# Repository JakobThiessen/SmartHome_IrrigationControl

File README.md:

# SmartHome_IrrigationControl

test

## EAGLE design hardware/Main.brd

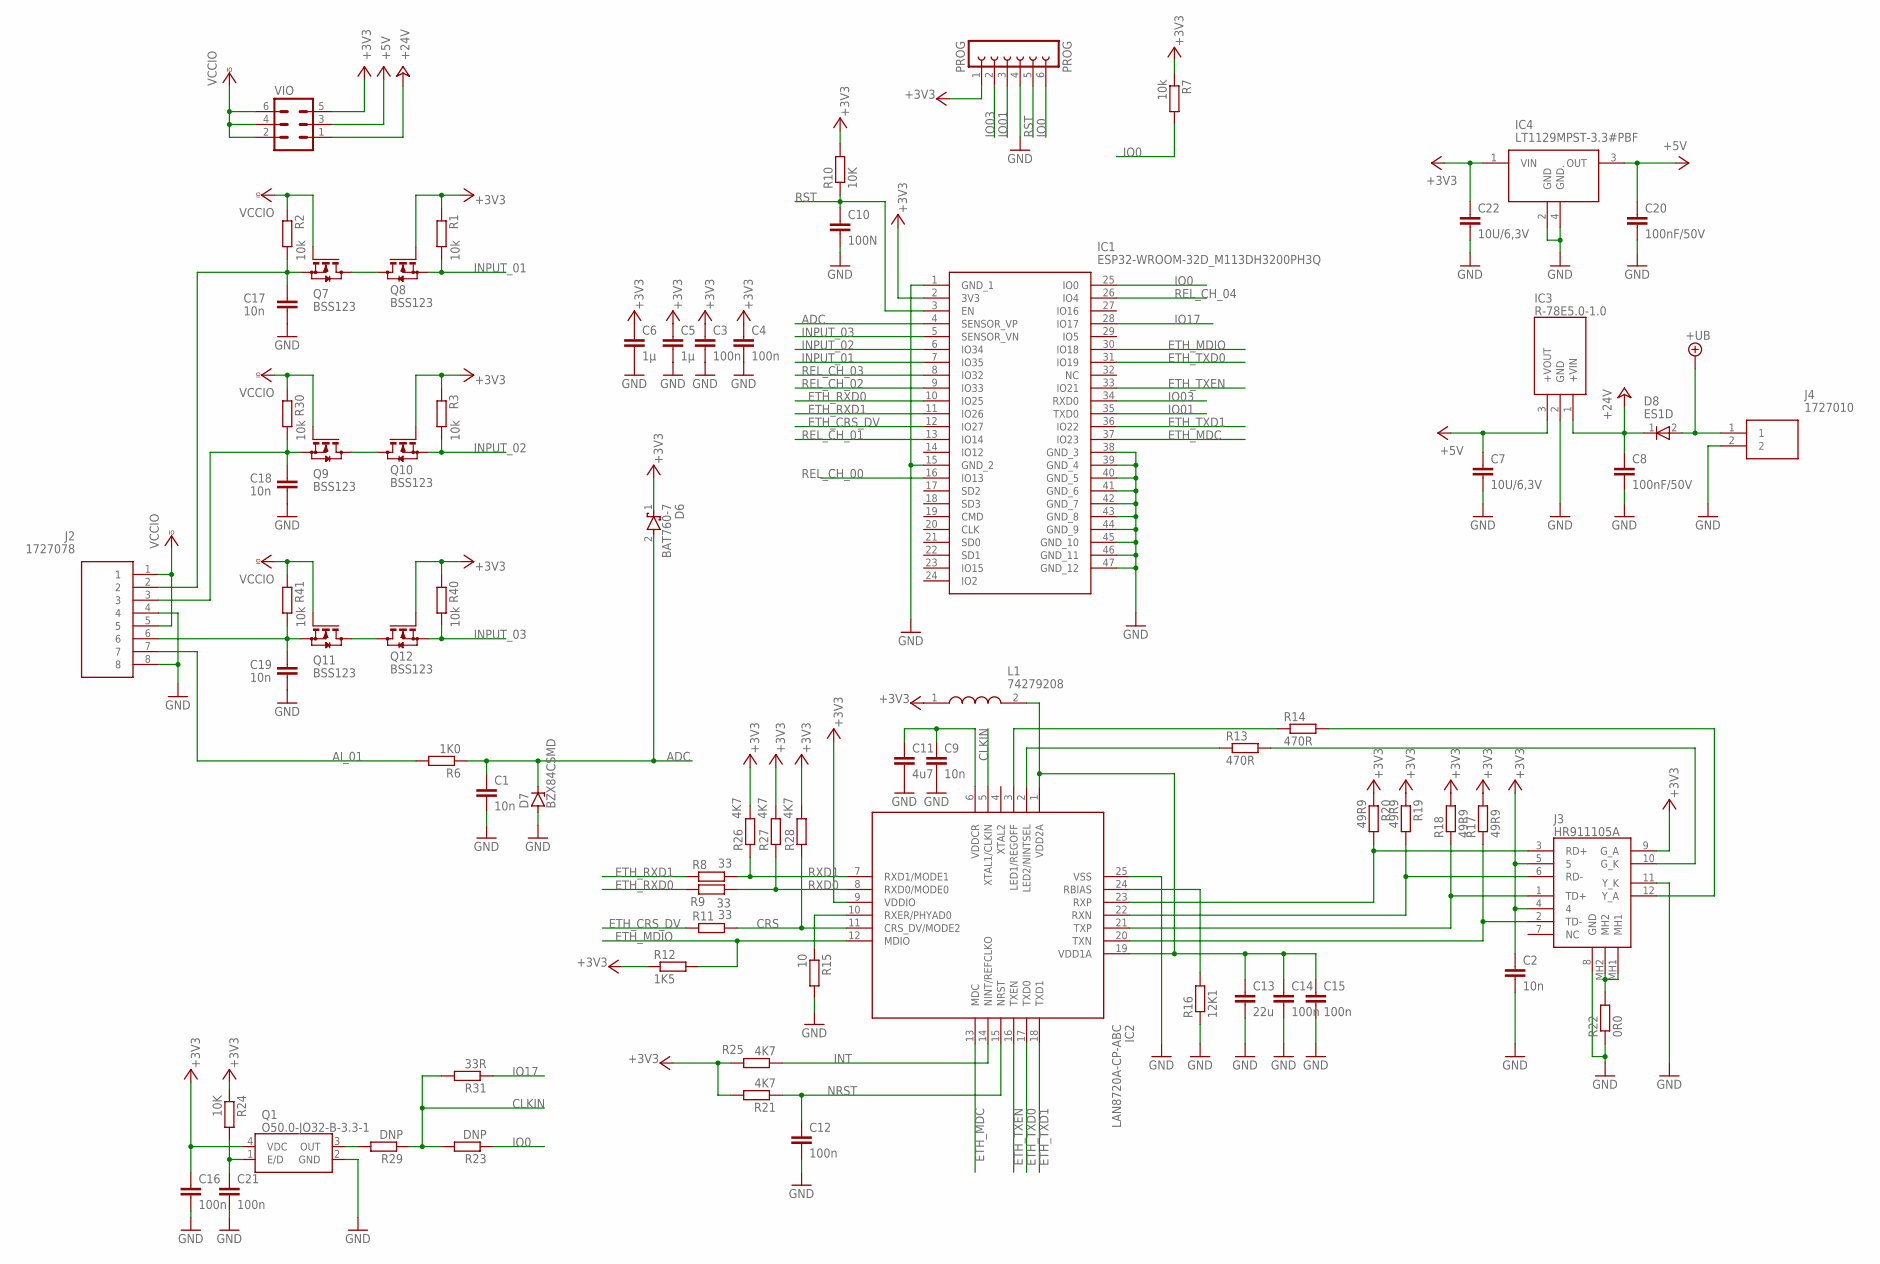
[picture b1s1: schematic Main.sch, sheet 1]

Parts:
C1, C2, C9, C17, C18, C19: 10n; C0603
C3, C4, C12, C14, C15, C16, C21: 100n; C0603
C5, C6: 1µ; C0603
C7, C22: 10U/6,3V; C0603
C8, C20: 100nF/50V; C0603
C10: 100N; C0603
C11: 4u7; C0603
C13: 22u; C0603
D6: BAT760-7; SOD2513X120N
D7: BZX84CSMD; TO236
D8: ES1D; SODFL3618X143N
IC1: ESP32-WROOM-32D_M113DH3200PH3Q; ESP32WROOM32DM113DH3200PH3Q0
IC2: LAN8720A-CP-ABC; QFN50P400X400X100-25N
IC3: R-78E5.0-1.0; R78E3310
IC4: LT1129MPST-3.3#PBF; SOT230P700X180-4N
J2: 1727078
J3: HR911105A
J4: 1727010
L1: 74279208; CAPC2012X90N
PROG: PROG; FE06
Q1: O50.0-JO32-B-3.3-1; O200JO32B1V31T1LF
Q7, Q8, Q9, Q10, Q11, Q12: BSS123; SOT23
R1, R2, R3, R7, R30, R40, R41: 10k; R0603
R6: 1K0; R0603
R8, R9, R11: 33; R0603
R10, R24: 10K; R0603
R12: 1K5; R0603
R13, R14: 470R; R0603
R15: 10; R0603
R16: 12K1; R0603
R17, R18, R19, R20: 49R9; R0603
R21, R25, R26, R27, R28: 4K7; R0603
R22: 0R0; R0603
R23, R29: DNP; R0603
R31: 33R; R0603
VIO: MA03-2

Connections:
+3V3: C2.1, C3.1, C4.1, C5.1, C6.1, C16.1, C22.1, D6.1 (K), IC1.2 (3V3), IC2.9 (VDDIO), IC4.1 (VIN), J3.4, J3.5, J3.9 (G_A), L1.1, PROG.1, Q1.4 (VDC), Q8.1 (G), Q10.1 (G), Q12.1 (G), R1.1, R3.1, R7.1, R10.2, R12.1, R17.2, R18.2, R19.1, R20.1, R21.2, R24.1, R25.2, R26.2, R27.2, R28.2, R40.1, VIO.5
+5V: C7.1, C20.1, IC3.3 (+VOUT), IC4.3 (OUT), VIO.3; also elsewhere on the board
+24V: C8.1, D8.1 (K), IC3.1 (+VIN), VIO.1
+UB: D8.2 (A), J4.1; also elsewhere on the board
ADC: C1.1, D6.2 (A), D7.C, IC1.4 (SENSOR_VP), R6.1
AI_01: J2.7, R6.2
CLKIN: IC2.5 (XTAL1/CLKIN), R23.2, R29.1, R31.2
CRS: IC2.11 (CRS_DV/MODE2), R11.2, R28.1
ETH_CRS_DV: IC1.12 (IO27), R11.1
ETH_MDC: IC1.37 (IO23), IC2.13 (MDC)
ETH_MDIO: IC1.30 (IO18), IC2.12 (MDIO), R12.2
ETH_PHY_PWR: C21.1, Q1.1 (E/D), R24.2
ETH_RXD0: IC1.10 (IO25), R9.1
ETH_RXD1: IC1.11 (IO26), R8.1
ETH_TXD0: IC1.31 (IO19), IC2.17 (TXD0)
ETH_TXD1: IC1.36 (IO22), IC2.18 (TXD1)
ETH_TXEN: IC1.33 (IO21), IC2.16 (TXEN)
GND: C1.2, C2.2, C3.2, C4.2, C5.2, C6.2, C7.2, C8.2, C9.2, C10.2, C11.2, C12.2, C13.2, C14.2, C15.2, C16.2, C17.2, C18.2, C19.2, C20.2, C21.2, C22.2, D7.A, IC1.1 (GND_1), IC1.15 (GND_2), IC1.38 (GND_3), IC1.39 (GND_4), IC1.40 (GND_5), IC1.41 (GND_6), IC1.42 (GND_7), IC1.43 (GND_8), IC1.44 (GND_9), IC1.45 (GND_10), IC1.46 (GND_11), IC1.47 (GND_12), IC2.25 (VSS), IC3.2 (GND), IC4.2 (GND), IC4.4 (GND.), J2.4, J2.8, J3.8 (GND), J3.11 (Y_K), J4.2, PROG.4, Q1.2 (GND), R15.2, R16.1, R22.1; also elsewhere on the board
INPUT_01: IC1.7 (IO35), Q8.2 (S), R1.2
INPUT_02: IC1.6 (IO34), Q10.2 (S), R3.2
INPUT_03: IC1.5 (SENSOR_VN), Q12.2 (S), R40.2
INT: IC2.14 (NINT/REFCLKO), R25.1
IO0: IC1.25 (IO0), PROG.6, R7.2, R23.1
IO01: IC1.35 (TXD0), PROG.3
IO03: IC1.34 (RXD0), PROG.2
IO17: IC1.28 (IO17), R31.1
unnamed: IC2.20 (TXN), J3.2 (TD-), R17.1
unnamed: IC2.22 (RXN), J3.6 (RD-), R19.2
unnamed: IC2.23 (RXP), J3.3 (RD+), R20.2
unnamed: J3.12 (Y_A), R14.2
unnamed: J3.10 (G_K), R13.2
unnamed: Q1.3 (OUT), R29.2
unnamed: J3.MH1, J3.MH2, R22.2
unnamed: Q7.3 (D), Q8.3 (D)
unnamed: Q9.3 (D), Q10.3 (D)
unnamed: C17.1, J2.2, Q7.2 (S), R2.2
unnamed: C13.1, C14.1, C15.1, IC2.1 (VDD2A), IC2.19 (VDD1A), L1.2
unnamed: C9.1, C11.1, IC2.6 (VDDCR)
unnamed: IC2.2 (LED2/NINTSEL), R13.1
unnamed: IC2.3 (LED1/REGOFF), R14.1
unnamed: IC2.10 (RXER/PHYAD0), R15.1
unnamed: IC2.21 (TXP), J3.1 (TD+), R18.1
unnamed: IC2.24 (RBIAS), R16.2
unnamed: C18.1, J2.3, Q9.2 (S), R30.2
unnamed: Q11.3 (D), Q12.3 (D)
unnamed: C19.1, J2.6, Q11.2 (S), R41.2
NRST: C12.1, IC2.15 (NRST), R21.1
REL_CH_00: IC1.16 (IO13); also elsewhere on the board
REL_CH_01: IC1.13 (IO14); also elsewhere on the board
REL_CH_02: IC1.9 (IO33); also elsewhere on the board
REL_CH_03: IC1.8 (IO32); also elsewhere on the board
REL_CH_04: IC1.26 (IO4); also elsewhere on the board
RST: C10.1, IC1.3 (EN), PROG.5, R10.1
RXD0: IC2.8 (RXD0/MODE0), R9.2, R27.1
RXD1: IC2.7 (RXD1/MODE1), R8.2, R26.1
VCCIO: J2.1, J2.5, Q7.1 (G), Q9.1 (G), Q11.1 (G), R2.1, R30.1, R41.1, VIO.2, VIO.4, VIO.6

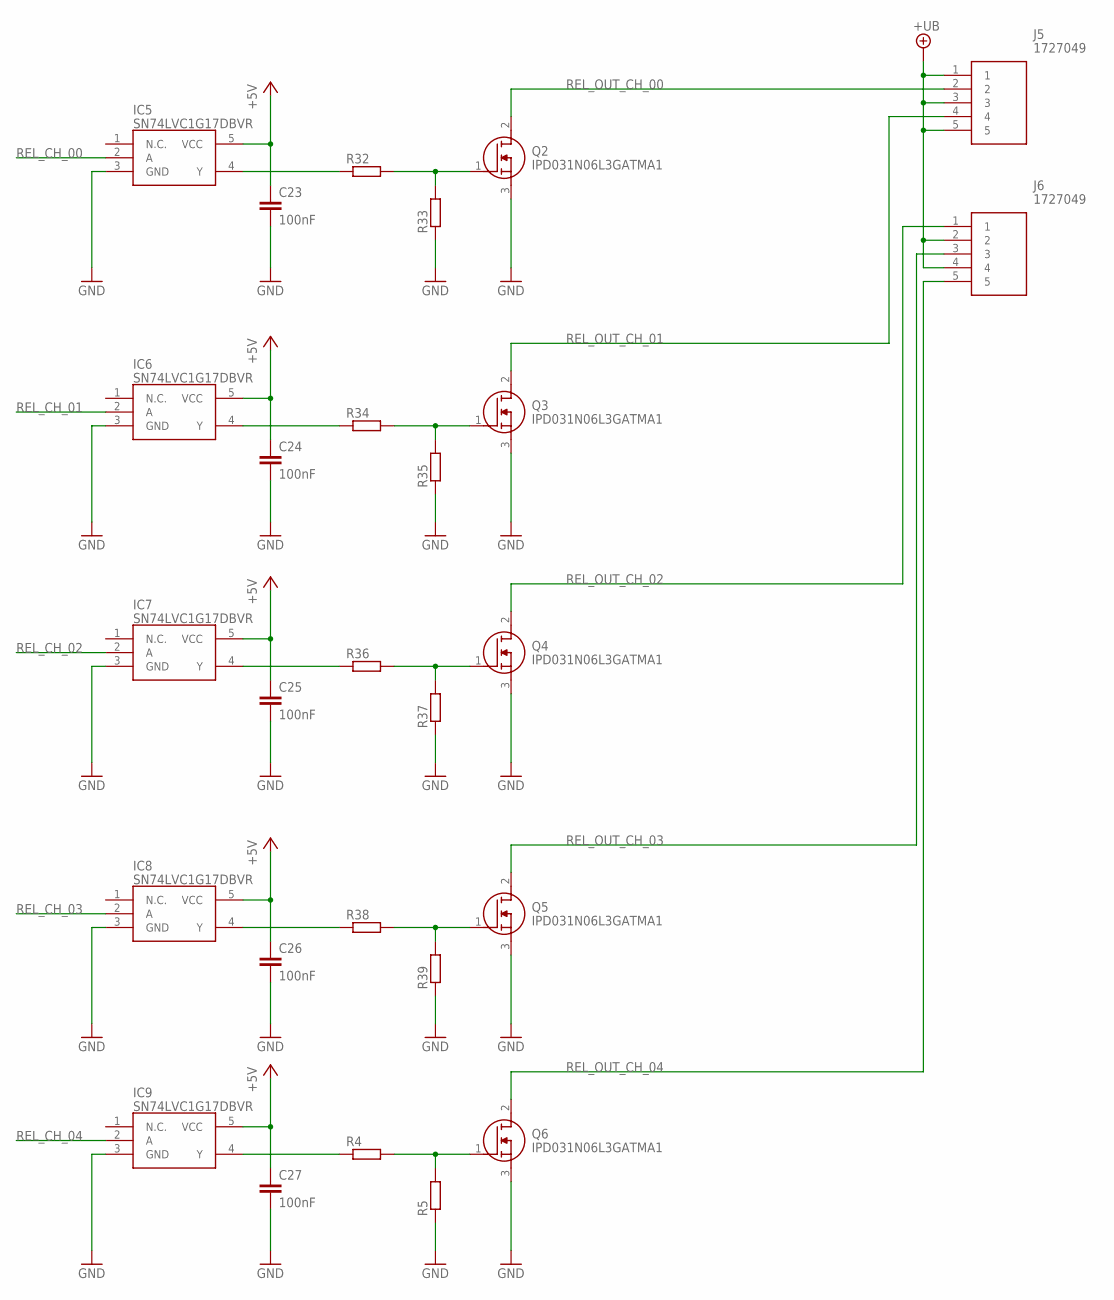
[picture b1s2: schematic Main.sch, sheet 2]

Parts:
C23, C24, C25, C26, C27: 100nF; C0603
IC5, IC6, IC7, IC8, IC9: SN74LVC1G17DBVR; SOT95P280X145-5N
J5, J6: 1727049
Q2, Q3, Q4, Q5, Q6: IPD031N06L3GATMA1
R4, R5, R32, R33, R34, R35, R36, R37, R38, R39: R-EU_R0603; R0603

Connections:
+5V: C23.1, C24.1, C25.1, C26.1, C27.1, IC5.5 (VCC), IC6.5 (VCC), IC7.5 (VCC), IC8.5 (VCC), IC9.5 (VCC); also elsewhere on the board
+UB: J5.1, J5.3, J5.5, J6.2, J6.4; also elsewhere on the board
GND: C23.2, C24.2, C25.2, C26.2, C27.2, IC5.3 (GND), IC6.3 (GND), IC7.3 (GND), IC8.3 (GND), IC9.3 (GND), Q2.3 (S), Q3.3 (S), Q4.3 (S), Q5.3 (S), Q6.3 (S), R5.1, R33.1, R35.1, R37.1, R39.1; also elsewhere on the board
unnamed: IC5.4 (Y), R32.1
unnamed: IC6.4 (Y), R34.1
unnamed: IC7.4 (Y), R36.1
unnamed: Q6.1 (G), R4.2, R5.2
unnamed: Q2.1 (G), R32.2, R33.2
unnamed: Q3.1 (G), R34.2, R35.2
unnamed: IC8.4 (Y), R38.1
unnamed: Q4.1 (G), R36.2, R37.2
unnamed: Q5.1 (G), R38.2, R39.2
unnamed: IC9.4 (Y), R4.1
REL_CH_00: IC5.2 (A); also elsewhere on the board
REL_CH_01: IC6.2 (A); also elsewhere on the board
REL_CH_02: IC7.2 (A); also elsewhere on the board
REL_CH_03: IC8.2 (A); also elsewhere on the board
REL_CH_04: IC9.2 (A); also elsewhere on the board
REL_OUT_CH_00: J5.2, Q2.2 (D)
REL_OUT_CH_01: J5.4, Q3.2 (D)
REL_OUT_CH_02: J6.1, Q4.2 (D)
REL_OUT_CH_03: J6.3, Q5.2 (D)
REL_OUT_CH_04: J6.5, Q6.2 (D)

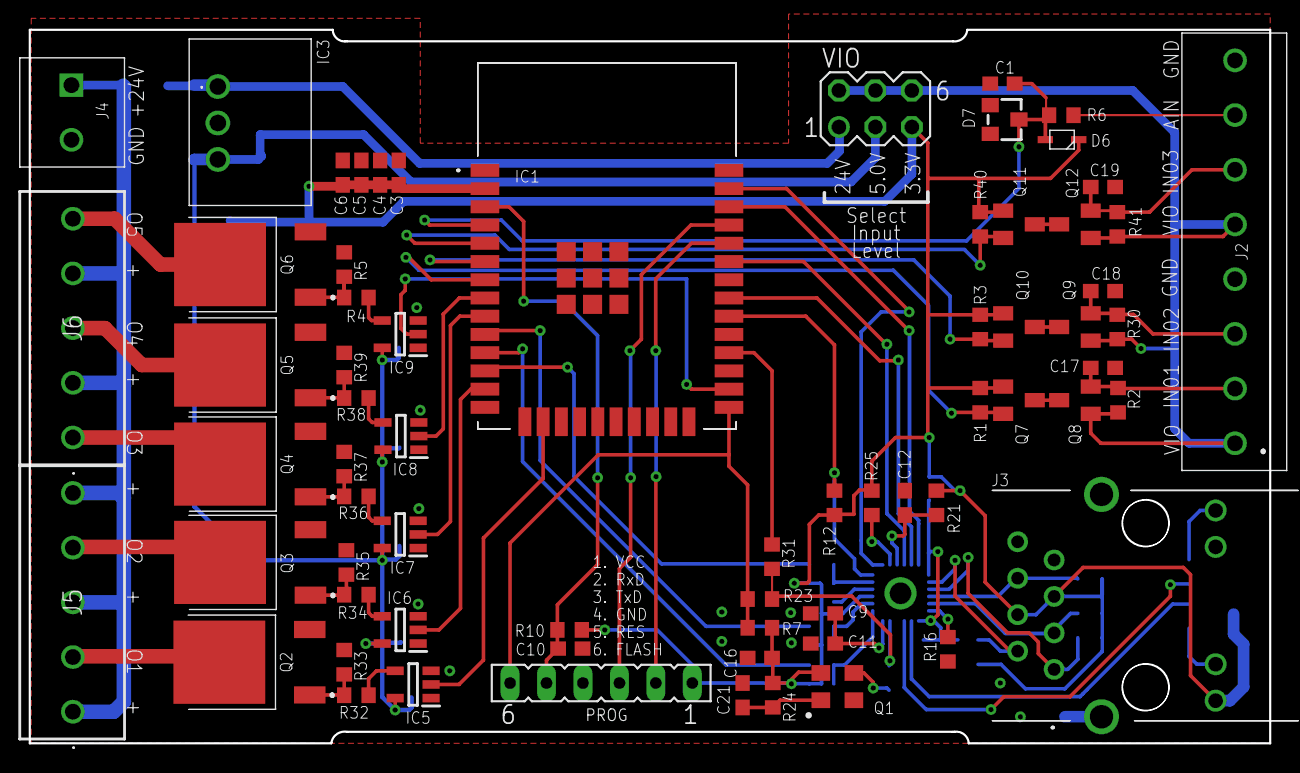
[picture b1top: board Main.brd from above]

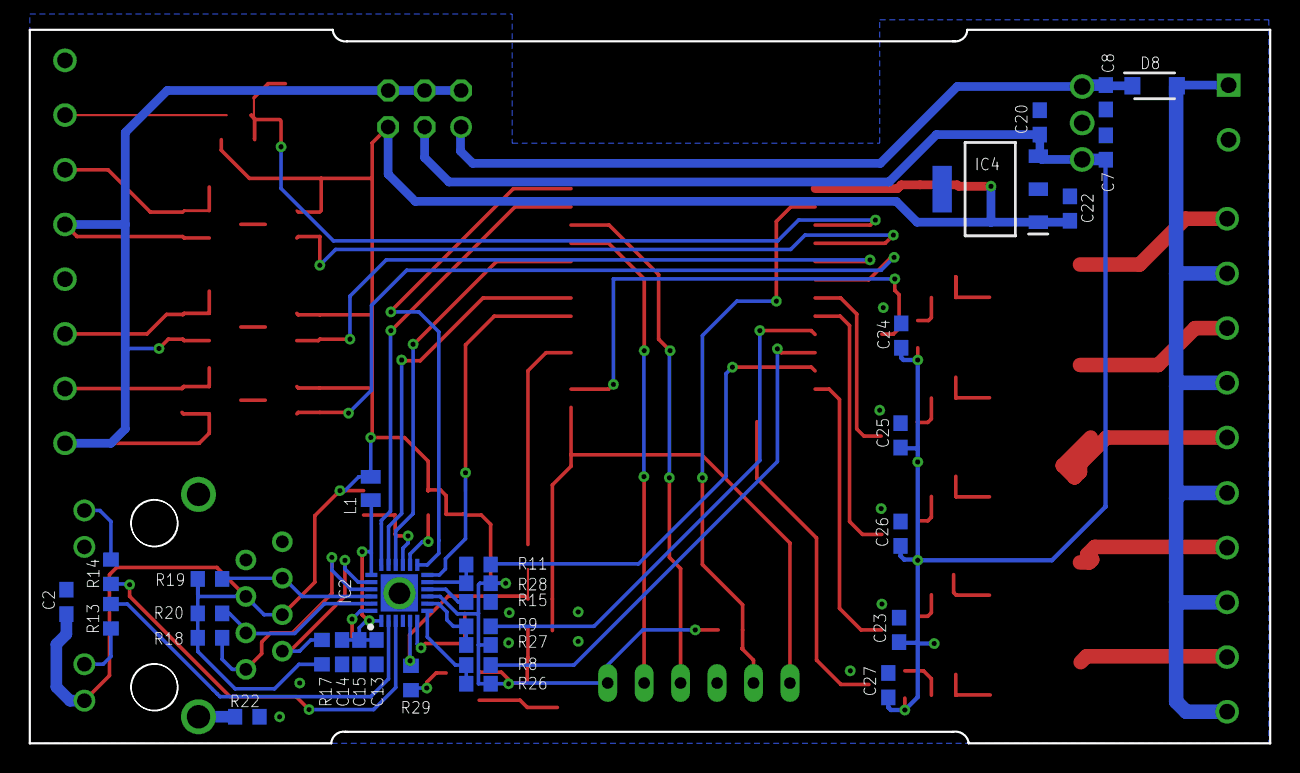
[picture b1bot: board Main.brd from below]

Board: 2 copper layers, 86.4 x 49.7 mm, 100 parts (32 on the bottom side), 71 nets.

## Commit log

2022-09-20 Layout fertig
2022-09-20 Bilder vom Layout aktualisiert
2022-09-20 gerber datei hinzugefügt
2022-09-27 1-gater ic statt 6 fach Treiber
2022-09-27 ein paar Änderungen in der Beschriftung
2022-10-01 Gerberdatei aktualisiert
2022-10-03 3d model angapasst
